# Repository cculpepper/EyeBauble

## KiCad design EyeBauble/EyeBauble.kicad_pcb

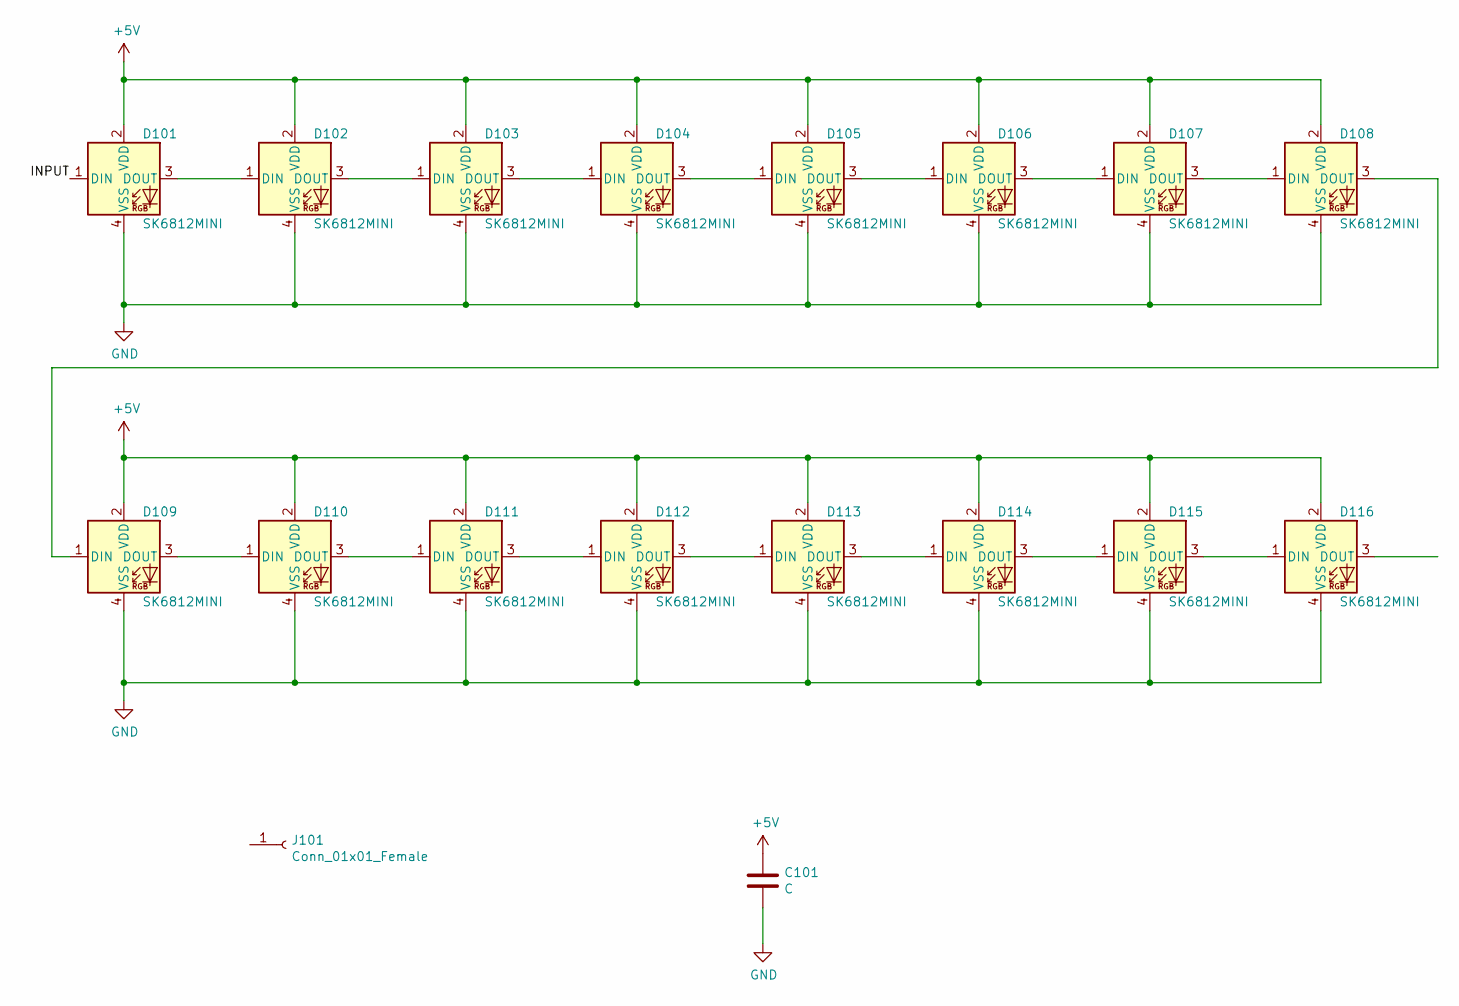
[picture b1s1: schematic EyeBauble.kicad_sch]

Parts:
C101: C; MountingHole_2.5mm
D101, D102, D103, D104, D105, D106, D107, D108, D109, D110, D111, D112, D113, D114, D115, D116: SK6812MINI; SK6812-EC1515
J101: Conn_01x01_Female; MountingHole_2.5mm

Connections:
+5V: C101.1, D101.2 (VDD), D102.2 (VDD), D103.2 (VDD), D104.2 (VDD), D105.2 (VDD), D106.2 (VDD), D107.2 (VDD), D108.2 (VDD), D109.2 (VDD), D110.2 (VDD), D111.2 (VDD), D112.2 (VDD), D113.2 (VDD), D114.2 (VDD), D115.2 (VDD), D116.2 (VDD)
/INPUT: D101.1 (DIN)
GND: C101.2, D101.4 (VSS), D102.4 (VSS), D103.4 (VSS), D104.4 (VSS), D105.4 (VSS), D106.4 (VSS), D107.4 (VSS), D108.4 (VSS), D109.4 (VSS), D110.4 (VSS), D111.4 (VSS), D112.4 (VSS), D113.4 (VSS), D114.4 (VSS), D115.4 (VSS), D116.4 (VSS)
unnamed: D101.3 (DOUT), D102.1 (DIN)
unnamed: D102.3 (DOUT), D103.1 (DIN)
unnamed: D103.3 (DOUT), D104.1 (DIN)
unnamed: D104.3 (DOUT), D105.1 (DIN)
unnamed: D105.3 (DOUT), D106.1 (DIN)
unnamed: D106.3 (DOUT), D107.1 (DIN)
unnamed: D107.3 (DOUT), D108.1 (DIN)
unnamed: D108.3 (DOUT), D109.1 (DIN)
unnamed: D109.3 (DOUT), D110.1 (DIN)
unnamed: D110.3 (DOUT), D111.1 (DIN)
unnamed: D111.3 (DOUT), D112.1 (DIN)
unnamed: D112.3 (DOUT), D113.1 (DIN)
unnamed: D113.3 (DOUT), D114.1 (DIN)
unnamed: D114.3 (DOUT), D115.1 (DIN)
unnamed: D115.3 (DOUT), D116.1 (DIN)

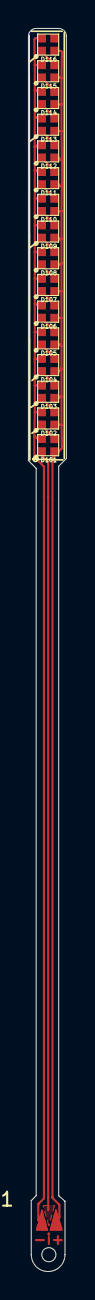
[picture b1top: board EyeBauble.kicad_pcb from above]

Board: 2 copper layers, 2.7 x 88.4 mm, 17 parts (0 on the bottom side), 17 nets.

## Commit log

2020-01-01 Commit before I destroy everything, submitted for fab revs all before this
2022-01-29 Dunno what I'm committing but this was the latest rev
